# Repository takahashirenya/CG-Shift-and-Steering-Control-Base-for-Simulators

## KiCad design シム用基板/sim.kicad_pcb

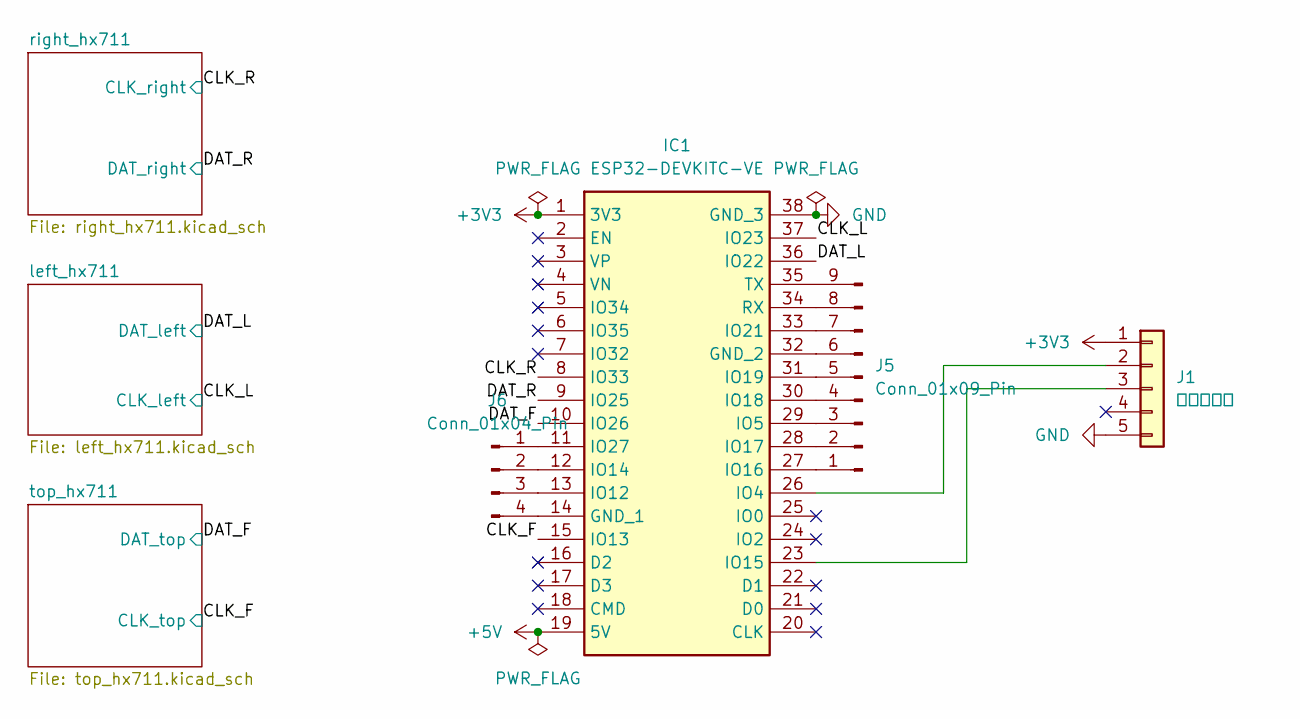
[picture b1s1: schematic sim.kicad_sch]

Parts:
IC1: ESP32-DEVKITC-VE; ESP32DEVKITCVE; Manufacturer_Part_Number ESP32-DEVKITC-VE; Mouser Part Number 356-ESP32-DEVKTC32VE
J1: ベースバー; JST_XH_B5B-XH-AM_1x05_P2.50mm_Vertical
J5: Conn_01x09_Pin; PinHeader_1x09_P2.54mm_Vertical
J6: Conn_01x04_Pin; PinHeader_1x04_P2.54mm_Vertical

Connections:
+3V3: IC1.1 (3V3), J1.1
+5V: IC1.19 (5V); also elsewhere on the board
/CLK_F: IC1.15 (IO13); also elsewhere on the board
/CLK_L: IC1.37 (IO23); also elsewhere on the board
/CLK_R: IC1.8 (IO33); also elsewhere on the board
/DAT_F: IC1.10 (IO26); also elsewhere on the board
/DAT_L: IC1.36 (IO22); also elsewhere on the board
/DAT_R: IC1.9 (IO25); also elsewhere on the board
GND: IC1.38 (GND_3), J1.5; also elsewhere on the board
unnamed: IC1.14 (GND_1), J6.4
unnamed: IC1.32 (GND_2), J5.6
unnamed: IC1.26 (IO4), J1.2
unnamed: IC1.29 (IO5), J5.3
unnamed: IC1.13 (IO12), J6.3
unnamed: IC1.12 (IO14), J6.2
unnamed: IC1.23 (IO15), J1.3
unnamed: IC1.27 (IO16), J5.1
unnamed: IC1.28 (IO17), J5.2
unnamed: IC1.30 (IO18), J5.4
unnamed: IC1.31 (IO19), J5.5
unnamed: IC1.33 (IO21), J5.7
unnamed: IC1.11 (IO27), J6.1
unnamed: IC1.34 (RX), J5.8
unnamed: IC1.35 (TX), J5.9

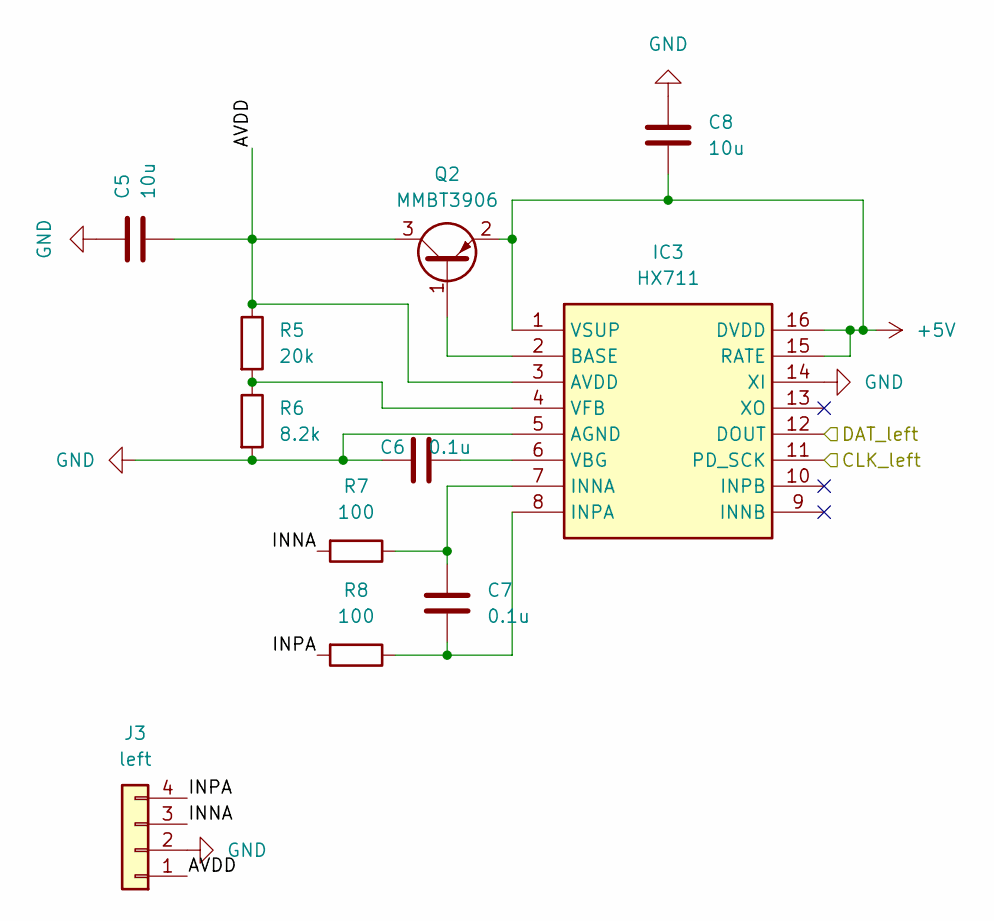
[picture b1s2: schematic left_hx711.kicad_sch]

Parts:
C5, C8: 10u; C_0603_1608Metric
C6, C7: 0.1u; C_0603_1608Metric
IC3: HX711; SOIC127P600X160-16N; Manufacturer_Part_Number HX711
J3: left; JST_XH_B4B-XH-AM_1x04_P2.50mm_Vertical
Q2: MMBT3906; SOT-23
R5: 20k; R_0603_1608Metric
R6: 8.2k; R_0603_1608Metric
R7, R8: 100; R_0603_1608Metric

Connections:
+5V: C8.2, IC3.1 (VSUP), IC3.15 (RATE), IC3.16 (DVDD), Q2.2 (E); also elsewhere on the board
/CLK_L: IC3.11 (PD_SCK); also elsewhere on the board
/DAT_L: IC3.12 (DOUT); also elsewhere on the board
/left_hx711/AVDD: C5.2, IC3.3 (AVDD), J3.1, Q2.3 (C), R5.1
/left_hx711/INNA: J3.3, R7.2
/left_hx711/INPA: J3.4, R8.2
GND: C5.1, C6.2, C8.1, IC3.5 (AGND), IC3.14 (XI), J3.2, R6.2; also elsewhere on the board
unnamed: IC3.2 (BASE), Q2.1 (B)
unnamed: C7.1, IC3.7 (INNA), R7.1
unnamed: C7.2, IC3.8 (INPA), R8.1
unnamed: C6.1, IC3.6 (VBG)
unnamed: IC3.4 (VFB), R5.2, R6.1

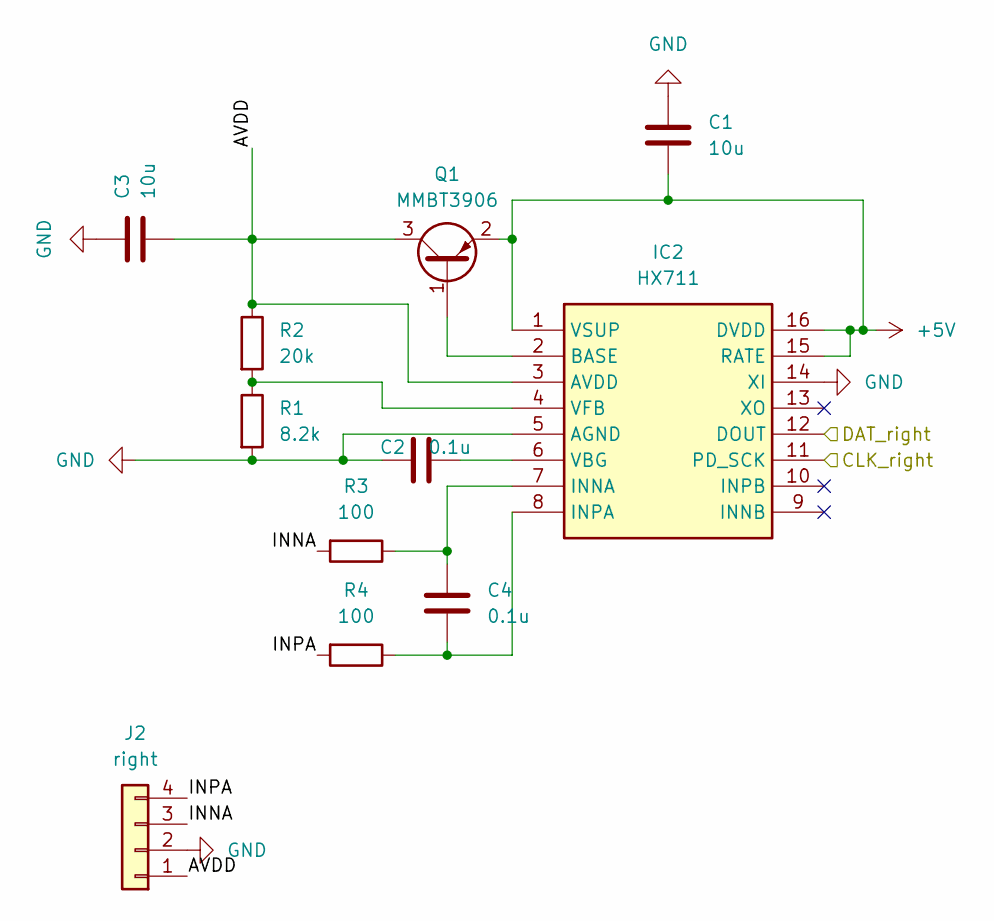
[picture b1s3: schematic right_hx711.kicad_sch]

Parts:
C1, C3: 10u; C_0603_1608Metric
C2, C4: 0.1u; C_0603_1608Metric
IC2: HX711; SOIC127P600X160-16N; Manufacturer_Part_Number HX711
J2: right; JST_XH_B4B-XH-AM_1x04_P2.50mm_Vertical
Q1: MMBT3906; SOT-23
R1: 8.2k; R_0603_1608Metric
R2: 20k; R_0603_1608Metric
R3, R4: 100; R_0603_1608Metric

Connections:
+5V: C1.2, IC2.1 (VSUP), IC2.15 (RATE), IC2.16 (DVDD), Q1.2 (E); also elsewhere on the board
/CLK_R: IC2.11 (PD_SCK); also elsewhere on the board
/DAT_R: IC2.12 (DOUT); also elsewhere on the board
/right_hx711/AVDD: C3.2, IC2.3 (AVDD), J2.1, Q1.3 (C), R2.1
/right_hx711/INNA: J2.3, R3.2
/right_hx711/INPA: J2.4, R4.2
GND: C1.1, C2.2, C3.1, IC2.5 (AGND), IC2.14 (XI), J2.2, R1.2; also elsewhere on the board
unnamed: IC2.2 (BASE), Q1.1 (B)
unnamed: C4.1, IC2.7 (INNA), R3.1
unnamed: C4.2, IC2.8 (INPA), R4.1
unnamed: C2.1, IC2.6 (VBG)
unnamed: IC2.4 (VFB), R1.1, R2.2

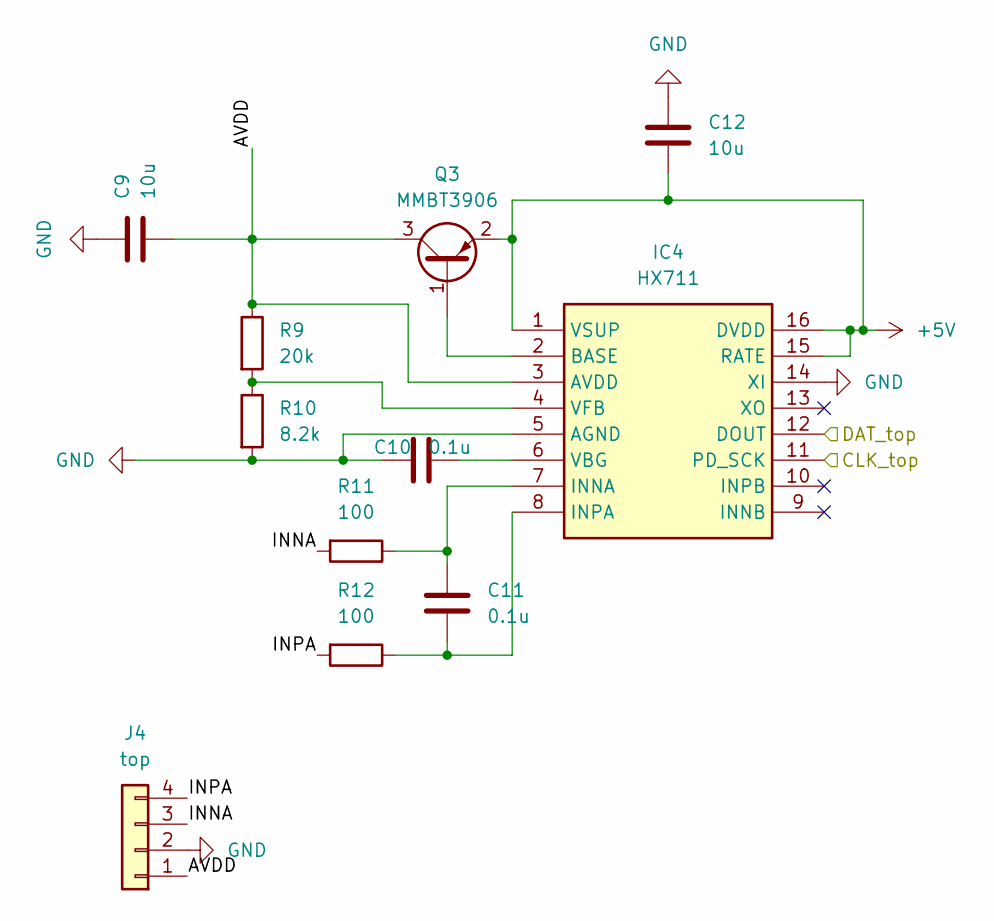
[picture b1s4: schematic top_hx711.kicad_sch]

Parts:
C9, C12: 10u; C_0603_1608Metric
C10, C11: 0.1u; C_0603_1608Metric
IC4: HX711; SOIC127P600X160-16N; Manufacturer_Part_Number HX711
J4: top; JST_XH_B4B-XH-AM_1x04_P2.50mm_Vertical
Q3: MMBT3906; SOT-23
R9: 20k; R_0603_1608Metric
R10: 8.2k; R_0603_1608Metric
R11, R12: 100; R_0603_1608Metric

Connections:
+5V: C12.2, IC4.1 (VSUP), IC4.15 (RATE), IC4.16 (DVDD), Q3.2 (E); also elsewhere on the board
/CLK_F: IC4.11 (PD_SCK); also elsewhere on the board
/DAT_F: IC4.12 (DOUT); also elsewhere on the board
/top_hx711/AVDD: C9.2, IC4.3 (AVDD), J4.1, Q3.3 (C), R9.1
/top_hx711/INNA: J4.3, R11.2
/top_hx711/INPA: J4.4, R12.2
GND: C9.1, C10.2, C12.1, IC4.5 (AGND), IC4.14 (XI), J4.2, R10.2; also elsewhere on the board
unnamed: IC4.2 (BASE), Q3.1 (B)
unnamed: C11.1, IC4.7 (INNA), R11.1
unnamed: C11.2, IC4.8 (INPA), R12.1
unnamed: C10.1, IC4.6 (VBG)
unnamed: IC4.4 (VFB), R9.2, R10.1

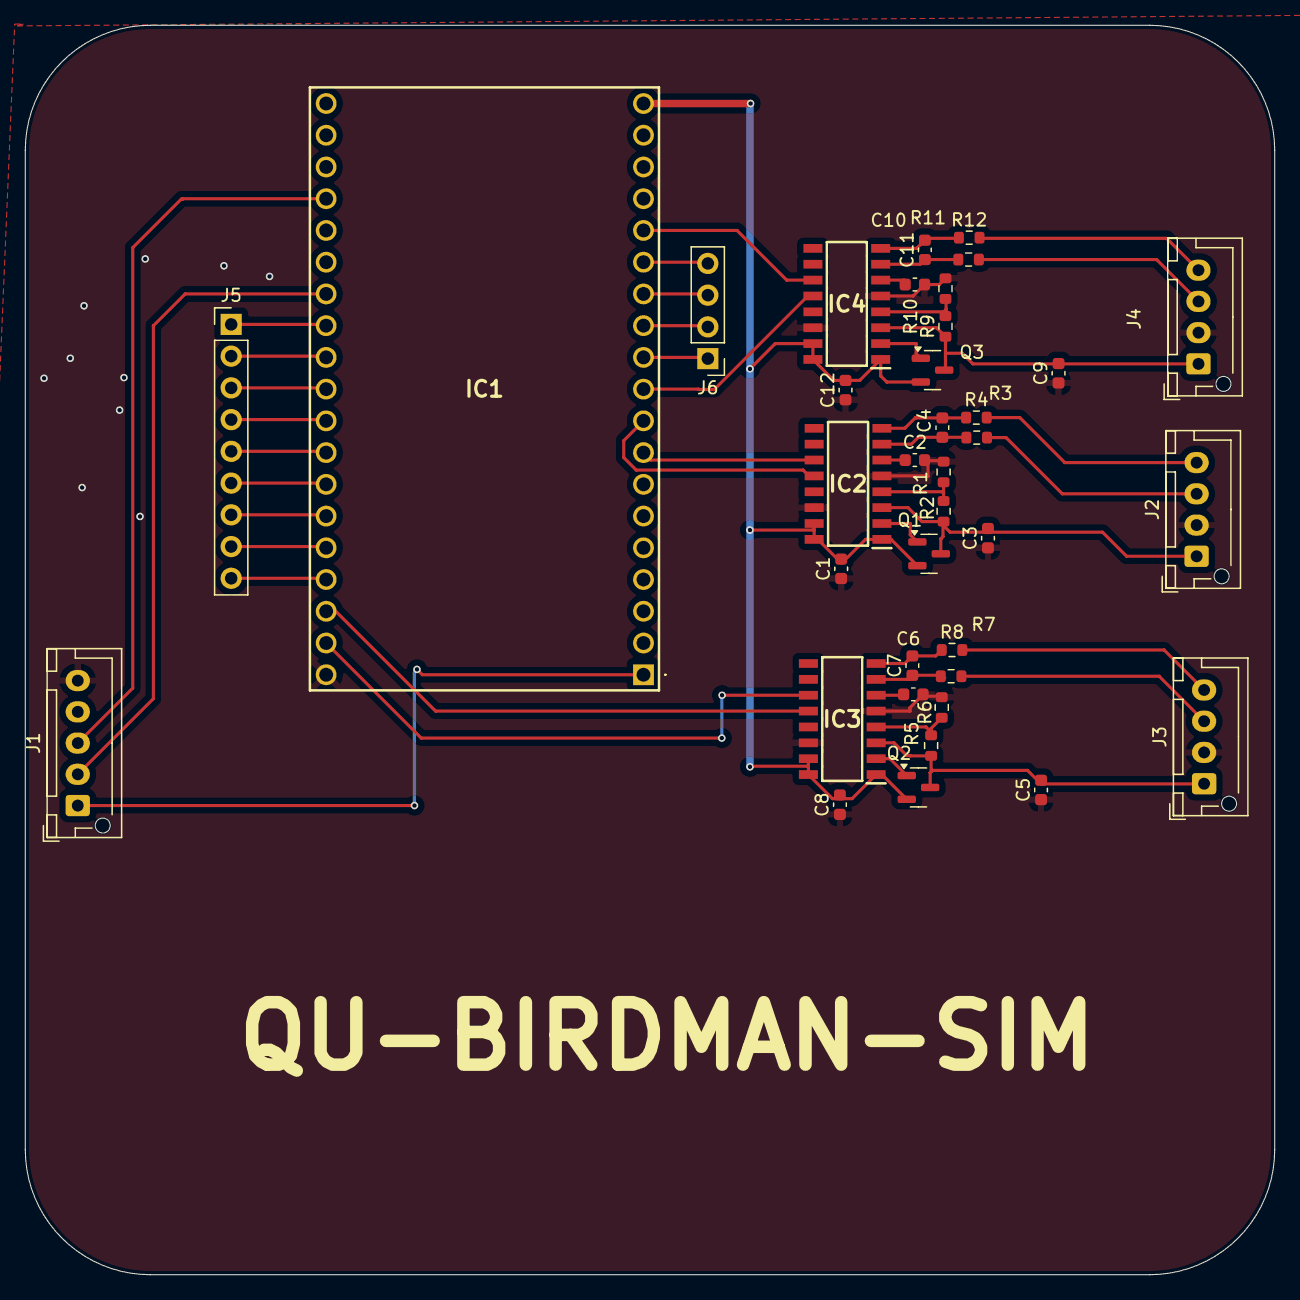
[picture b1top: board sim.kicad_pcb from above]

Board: 2 copper layers, 100.0 x 100.0 mm, 37 parts (0 on the bottom side), 48 nets.

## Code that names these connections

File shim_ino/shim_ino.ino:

#include <Arduino.h>

#define DAT_R 25
#define CLK_R 33
#define DAT_L 22
#define CLK_L 23
#define DAT_F 26
#define CLK_F 13
#define CONTROLLER_SUPPLY 21
#define PITCH_HIGH 4700
#define PITCH_LOW 1000
#define FAST_HIGH 14
#define FAST_LOW 10.3
#define SLOW_HIGH 9
#define SLOW_LOW 4
#define PERIOD_MINI 100
#define PERIOD_MAX 500

const int RUD_PIN = A13;
const int ELE_PIN = A10;
const int LED_PIN = 18;
const int BUZZER_PIN = 14;

float offset_front = 0;
float offset_right = 0;
float offset_left = 0;
float pilot_m = 14960.0;
float c_m = 8091.0;
float tail_length = 0.764;
float front_length = 1.0;
float zero_length = 0.0768;

String air_speed_data = "0.000";
float airspeed = 0;

// =====================
// 新BuzzerControllerクラス
// =====================
class BuzzerController {
public:
  BuzzerController(int pin)
    : buzzerPin(pin), lastBeepTime(0), beepOn(false), beepLength(0), beepPeriod(0), pitch(0), lastVal(-999) {
    pinMode(buzzerPin, OUTPUT);
  }

  void sound(float val) {
    unsigned long now = millis();

    // fast zone
    if (val > FAST_LOW) {
      pitch = PITCH_HIGH;
      beepPeriod = calcFastPeriod(val);
      beepLength = beepPeriod / 2;
      manageBeep(now);
    }
    // slow zone
    else if (SLOW_LOW < val && val < SLOW_HIGH) {
      pitch = PITCH_LOW;
      beepPeriod = calcSlowPeriod(val);
      beepLength = beepPeriod / 2;
      manageBeep(now);
    }
    // dead zone (silent)
    else {
      noTone(buzzerPin);
      beepOn = false;
      lastBeepTime = now;
    }
    lastVal = val;
  }

private:
  int buzzerPin;
  unsigned long lastBeepTime;
  bool beepOn;
  int beepLength;
  int beepPeriod;
  int pitch;
  float lastVal;

  int calcFastPeriod(float val) {
    if (val >= FAST_HIGH) return PERIOD_MINI;
    float v = (val - FAST_LOW) / (FAST_HIGH - FAST_LOW);
    return (int)((PERIOD_MAX - PERIOD_MINI) * (1 - v) + PERIOD_MINI);
  }

  int calcSlowPeriod(float val) {
    if (val < SLOW_LOW) return PERIOD_MINI;
    float v = (val - SLOW_LOW) / (SLOW_HIGH - SLOW_LOW);
    return (int)((PERIOD_MAX - PERIOD_MINI) * v + PERIOD_MINI);
  }

  void manageBeep(unsigned long now) {
    if (!beepOn && (now - lastBeepTime >= beepPeriod)) {
      tone(buzzerPin, pitch, beepLength); // ピーッ
      beepOn = true;
      lastBeepTime = now;
    }
    if (beepOn && (now - lastBeepTime >= beepLength)) {
      noTone(buzzerPin);
      beepOn = false;
    }
  }
};

BuzzerController buzzer(BUZZER_PIN);

// ========================
// その他の関数・setup/loop
// ========================

void setup() {
  Serial.begin(115200);
  Serial2.begin(115200);
  Serial.println("start");
  pinMode(DAT_R, INPUT);
  pinMode(CLK_R, OUTPUT);
  pinMode(DAT_L, INPUT);
  pinMode(CLK_L, OUTPUT);
  pinMode(DAT_F, INPUT);
  pinMode(CLK_F, OUTPUT);
  pinMode(RUD_PIN, INPUT);
  pinMode(ELE_PIN, INPUT);
  pinMode(CONTROLLER_SUPPLY, OUTPUT);
  pinMode(LED_PIN, OUTPUT);
  digitalWrite(LED_PIN, HIGH);
  digitalWrite(CONTROLLER_SUPPLY, HIGH);
  xTaskCreatePinnedToCore(loo1, "loo1", 8192, NULL, 1, NULL, 0);

  offset_front = Read(CLK_F, DAT_F);
  offset_right = Read(CLK_R, DAT_R);
  offset_left = Read(CLK_L, DAT_L);
}

void loo1(void* pvParameters) {
  while (1) {
    airspeed = air_speed_data.toFloat();
    buzzer.sound(airspeed);
    delay(5); // 5msに変更（あまり短すぎても意味ないため）
  }
}

int applyDeadZone(int value, int deadZone = 3) {
  return (value > -deadZone && value < deadZone) ? 0 : value;
}

void loop() {
  float data_front = Read(CLK_F, DAT_F);
  txrx();
  float data_right = Read(CLK_R, DAT_R);
  txrx();
  float data_left = Read(CLK_L, DAT_L);
  txrx();
  float ans_f = offset_front - data_front;
  float ans_r = offset_right - data_right;
  float ans_l = offset_left - data_left;
  float total = ans_f +  ( ans_r * 2  ) ;
  txrx();
  int rud = map(analogRead(RUD_PIN), 0, 3600, 11, -10);
  int ele = map(analogRead(ELE_PIN), 1000, 2800, -10, 9);
  txrx();
  float x = (ans_f * front_length) / total;
  int pilot_cog = 1000 * x;
  char str[100];
  sprintf(str, "%d,%d,%d", -applyDeadZone(ele), -applyDeadZone(rud), 320);
  txrx();
  Serial.println(str);
  txrx();
}

void txrx() {
  if (Serial.available() > 0) {
    String air_data = Serial.readStringUntil(13);
    Serial.read();
    Serial2.println(air_data);
    String dataArray[18];
    int index = 0;
    int startIndex = 0;
    int endIndex = air_data.indexOf(',', startIndex);
    while (endIndex != -1) {
      dataArray[index++] = air_data.substring(startIndex, endIndex);
      startIndex = endIndex + 1;
      endIndex = air_data.indexOf(',', startIndex);
    }
    dataArray[index] = air_data.substring(startIndex);
    air_speed_data = dataArray[4];
  }
}

float Read(int CLK, int DAT) {
  long sum = 0;
  for (int i = 0; i < 3; i++) {
    long data = 0;
    while (digitalRead(DAT) != 0)
      ;
    for (char i = 0; i < 24; i++) {
      digitalWrite(CLK, 1);
      delayMicroseconds(1);
      digitalWrite(CLK, 0);
      delayMicroseconds(1);
      data = (data << 1) | (digitalRead(DAT));
    }
    digitalWrite(CLK, 1);
    delayMicroseconds(1);
    digitalWrite(CLK, 0);
    delayMicroseconds(1);
    data = data ^ 0x800000;
    sum += data;
  }
  float data = sum / 3;
  float volt = data * (4.2987 / 16777216.0 / 128);
  return volt / (0.001 * 4.2987 / 20000.0);
}

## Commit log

2025-12-04 25/12/04
